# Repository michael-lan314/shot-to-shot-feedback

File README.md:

# Shot to shot feedback box
Programmable electronic boxes for discrete time PID feedback between experimental shots for ultracold atomic experiment. This low cost, plug-and-play device corrects for slow drifts in experimental parameters to keep shots consistent.

Feedback is performed as follows: an error signal from the experiment is fed into a Red Pitaya board, which calculates feedback and outputs an analog voltage. Then, using a PCB summing amplifier, this voltage offsets the external experimental setpoint. Thus, this repo includes feedback code for the Red Pitaya, the PCB design, and the CAD design for a case.

# Parts list
- Red Pitaya (STEMLab 125-14)
- Dual noninverting summing amplifier board (design in repo, needs parts)
- 3D printed enclosure: (CAD files in repo)

### PCB construction
An analog adder (inverting adder + unity gain inverter) is used to add the Red Pitaya output back into the experiment. The basic schematic for one channel is shown below, where the choice of resistors will depend on the desired input/output voltage ratios.

The full board, with schematic and design in the repo, consists of two such channels with an added power supply and optional capacitors for stability. One board requires the following parts:
- 2x AD706JNZ dual op amp (through-hole)
- 2x 90 degree SMA connector (PCB.SMAFRA.HT on Digikey)
- 6x 90 degree BNC connector (5227161-1 on Digikey)
- various resistors (through-hole).
- 0.33 uF capacitors

# Redpitaya instructions
### setup, packages
1. Install Red Pitaya software and connect to network ([link](https://redpitaya.readthedocs.io/en/latest/quickStart/OS_update/OS_update.html), [link](https://redpitaya.readthedocs.io/en/latest/developerGuide/software/console/ssh/ssh.html))
2. Install project-specific Red Pitaya package: (___)
3. Through the remote connection, copy feedback C code to desired Red Pitaya folder and compile

# Usage
set up trigger on __ channel

### modular code
While all types of feedback will have the same general structure, the error signal input, feedback logic, and output will be different for each use case. Thus the C code includes multiple input, feedback, and output modules that are called by (main).

### examples
#### Tweezer position feedback
#### Sideprobe frequency feedback

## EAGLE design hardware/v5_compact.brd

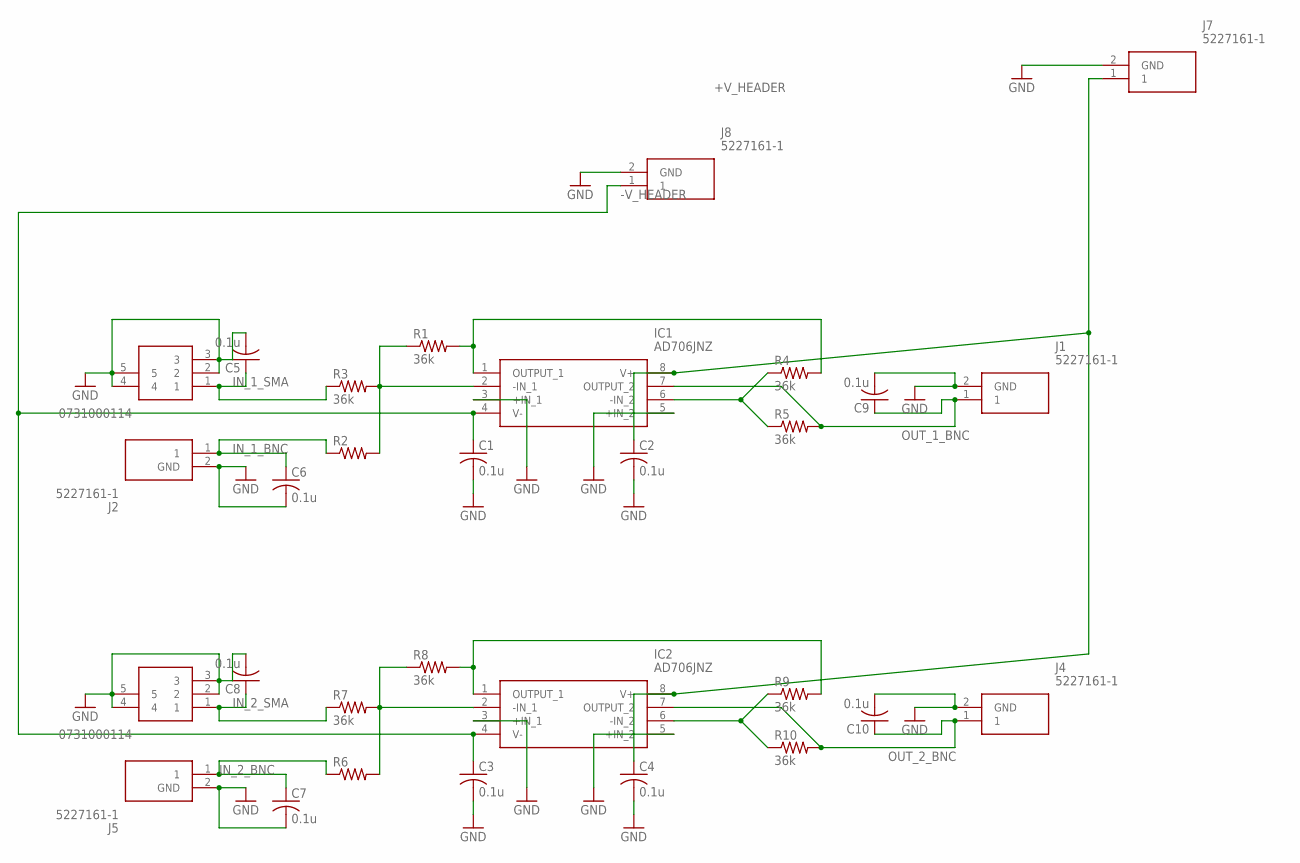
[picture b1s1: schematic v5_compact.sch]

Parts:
C1, C2, C3, C4, C5, C6, C7, C8, C9, C10: 0.1u; C050-025X075
IC1, IC2: AD706JNZ; DIP794W56P254L959H533Q8N
J1, J2, J4, J5, J7, J8: 5227161-1; 52271611
J3, J6: 0731000114
R1, R3, R4, R5, R7, R8, R9, R10: 36k; 0207/10
R2, R6: R-US_0207/10; 0207/10

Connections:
+V_HEADER: C2.1, C4.1, IC1.8 (V+), IC2.8 (V+), J7.1
-V_HEADER: C1.1, C3.1, IC1.4 (V-), IC2.4 (V-), J8.1
GND: C1.2, C2.2, C3.2, C4.2, C5.2, C6.2, C7.2, C8.2, C9.2, C10.2, IC1.3 (+IN_1), IC1.5 (+IN_2), IC2.3 (+IN_1), IC2.5 (+IN_2), J1.2 (GND), J2.2 (GND), J3.2, J3.3, J3.4, J3.5, J4.2 (GND), J5.2 (GND), J6.2, J6.3, J6.4, J6.5, J7.2 (GND), J8.2 (GND)
IN_1_BNC: C6.1, J2.1, R2.1
IN_1_SMA: C5.1, J3.1, R3.1
IN_2_BNC: C7.1, J5.1, R6.1
IN_2_SMA: C8.1, J6.1, R7.1
unnamed: IC1.2 (-IN_1), R1.1, R2.2, R3.2
unnamed: IC1.1 (OUTPUT_1), R1.2, R4.2
unnamed: IC1.6 (-IN_2), R4.1, R5.1
unnamed: IC2.2 (-IN_1), R6.2, R7.2, R8.1
unnamed: IC2.6 (-IN_2), R9.1, R10.1
unnamed: IC2.1 (OUTPUT_1), R8.2, R9.2
OUT_1_BNC: C9.1, IC1.7 (OUTPUT_2), J1.1, R5.2
OUT_2_BNC: C10.1, IC2.7 (OUTPUT_2), J4.1, R10.2

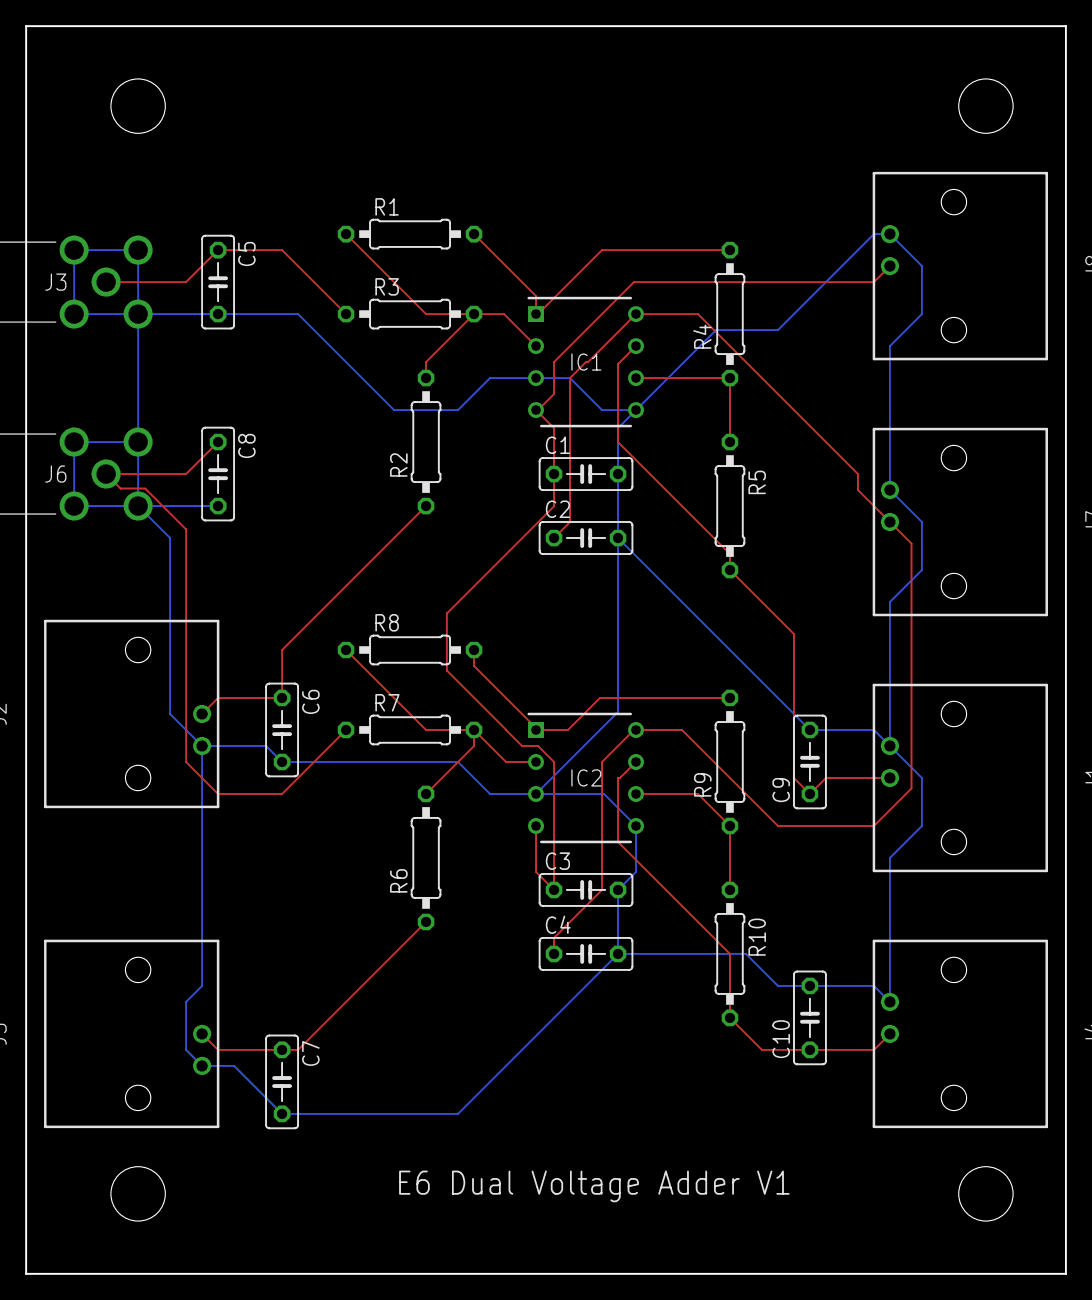
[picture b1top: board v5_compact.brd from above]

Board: 2 copper layers, 82.5 x 99.1 mm, 30 parts (0 on the bottom side), 15 nets.
